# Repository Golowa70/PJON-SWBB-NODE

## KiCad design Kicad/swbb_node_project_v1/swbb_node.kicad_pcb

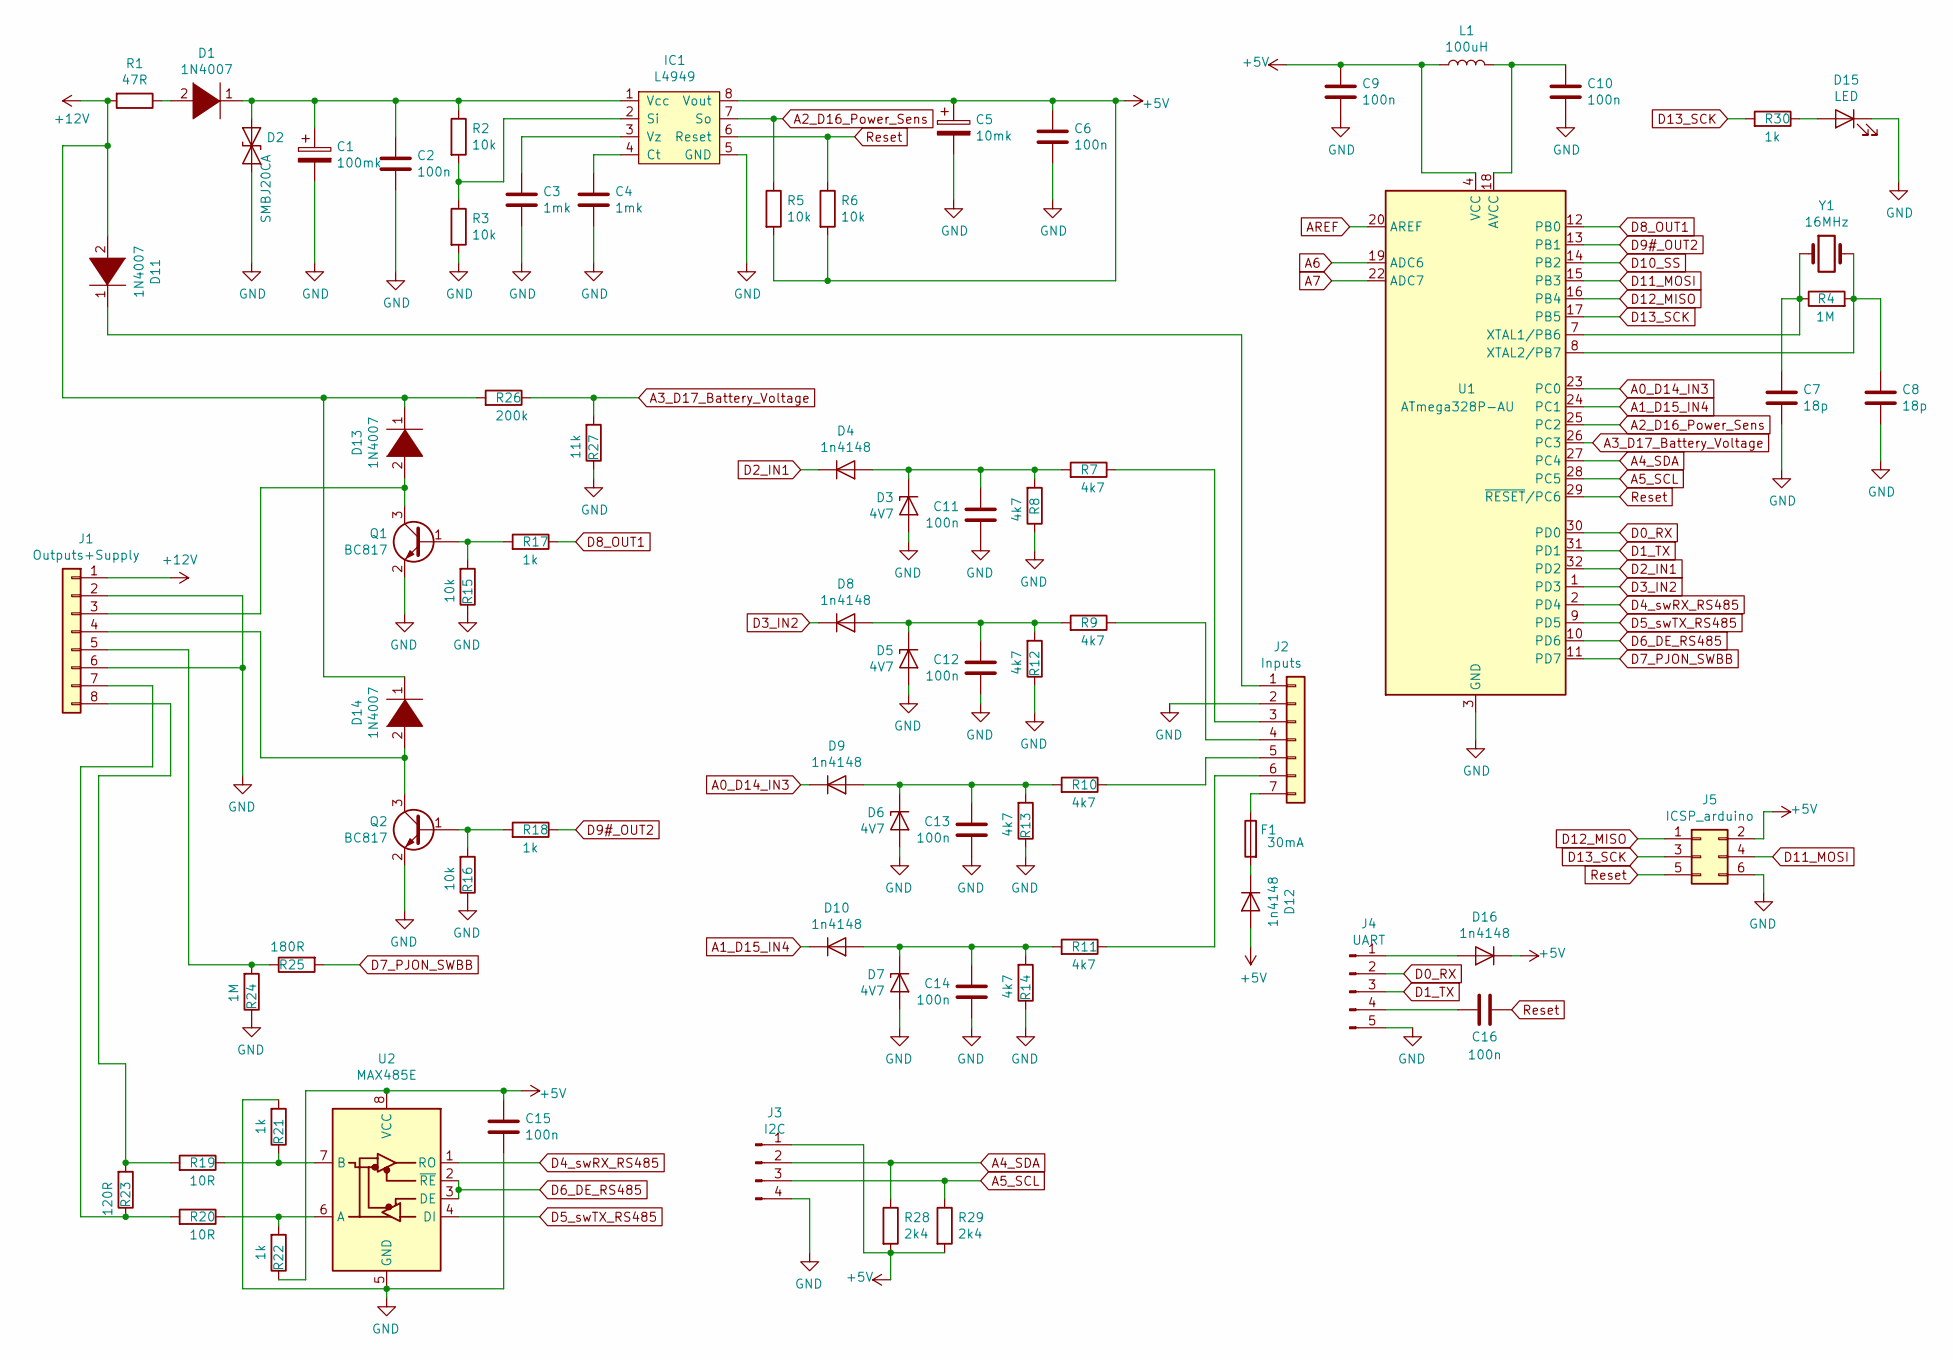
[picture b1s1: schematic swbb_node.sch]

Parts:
C1: 100mk; C_Elec_6.3x7.7
C2, C6, C9, C10, C11, C12, C13, C14, C15: 100n; C_0805_2012Metric
C3, C4: 1mk; C_1206_3216Metric
C5: 10mk; CP_EIA-7343-31_Kemet-D
C7, C8: 18p; C_1206_3216Metric
C16: 100n; C_0805_2012Metric_Pad1.15x1.40mm_HandSolder
D1, D11, D13, D14: 1N4007; D_SOD-123
D2: SMBJ20CA; D_SMB_Handsoldering
D3, D5, D6, D7: 4V7; D_1206_3216Metric_Pad1.42x1.75mm_HandSolder
D4, D8, D9, D10, D12, D16: 1n4148; D_1206_3216Metric_Pad1.42x1.75mm_HandSolder
D15: LED; LED_D3.0mm
F1: 30mA; Fuse_2010_5025Metric
IC1: L4949; SOIC-8_3.9x4.9mm_P1.27mm
J1: Outputs+Supply; JST_EH_S8B-EH_1x08_P2.50mm_Horizontal
J2: Inputs; JST_EH_S7B-EH_1x07_P2.50mm_Horizontal
J3: I2C; PinHeader_1x04_P2.54mm_Vertical
J4: UART; PinHeader_1x05_P2.54mm_Vertical
J5: ICSP_arduino; PinHeader_2x03_P2.54mm_Vertical
L1: 100uH; L_1210_3225Metric_Pad1.42x2.65mm_HandSolder
Q1, Q2: BC817; SOT-23
R1: 47R; R_2512_6332Metric
R2, R5, R6, R15, R16: 10k; R_0805_2012Metric_Pad1.15x1.40mm_HandSolder
R3: 10k; R_0805_2012Metric
R4, R24: 1M; R_0805_2012Metric_Pad1.15x1.40mm_HandSolder
R7, R8, R9, R10, R11, R12, R13, R14: 4k7; R_0805_2012Metric_Pad1.15x1.40mm_HandSolder
R17, R18, R21, R22: 1k; R_0805_2012Metric_Pad1.15x1.40mm_HandSolder
R19, R20: 10R; R_1206_3216Metric_Pad1.42x1.75mm_HandSolder
R23: 120R; R_1206_3216Metric_Pad1.42x1.75mm_HandSolder
R25: 180R; R_0805_2012Metric_Pad1.15x1.40mm_HandSolder
R26: 200k; R_0805_2012Metric_Pad1.15x1.40mm_HandSolder
R27: 11k; R_0805_2012Metric_Pad1.15x1.40mm_HandSolder
R28, R29: 2k4; R_0603_1608Metric_Pad1.05x0.95mm_HandSolder
R30: 1k; R_0603_1608Metric_Pad1.05x0.95mm_HandSolder
U1: ATmega328P-AU; TQFP-32_7x7mm_P0.8mm
U2: MAX485E; SO-8_3.9x4.9mm_P1.27mm
Y1: 16MHz; Crystal_HC49-U_Vertical

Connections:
+5V: C5.1, C6.1, C9.1, C15.1, D12.2 (A), D16.1 (K), IC1.8 (Vout), J3.1, J5.2 (+5V), L1.1, R5.2, R6.2, R22.1, R28.2, R29.2, U1.4 (VCC), U1.6 (VCC), U2.8 (VCC)
+12V: D11.2 (K), D13.1 (A), D14.1 (A), J1.1, R1.2, R26.2
A0_D14_IN3: D9.1 (K), U1.23 (PC0)
A1_D15_IN4: D10.1 (K), U1.24 (PC1)
A2_D16_Power_Sens: IC1.7 (So), R5.1, U1.25 (PC2)
A3_D17_Battery_Voltage: R26.1, R27.2, U1.26 (PC3)
A4_SDA: J3.2, R28.1, U1.27 (PC4)
A5_SCL: J3.3, R29.1, U1.28 (PC5)
A6: U1.19 (ADC6)
A7: U1.22 (ADC7)
AREF: U1.20 (AREF)
D0_RX: J4.2, U1.30 (PD0)
D1_TX: J4.3, U1.31 (PD1)
D2_IN1: D4.1 (K), U1.32 (PD2)
D3_IN2: D8.1 (K), U1.1 (PD3)
D4_swRX_RS485: U1.2 (PD4), U2.1 (RO)
D5_swTX_RS485: U1.9 (PD5), U2.4 (DI)
D6_DE_RS485: U1.10 (PD6), U2.2 (~RE), U2.3 (DE)
D7_PJON_SWBB: R25.2, U1.11 (PD7)
D8_OUT1: R17.1, U1.12 (PB0)
D9#_OUT2: R18.1, U1.13 (PB1)
D10_SS: U1.14 (PB2)
D11_MOSI: J5.4 (D11/MOSI), U1.15 (PB3)
D12_MISO: J5.1 (D12/MISO), U1.16 (PB4)
D13_SCK: J5.3 (D13/SCK), R30.2, U1.17 (PB5)
GND: C1.2, C2.2, C3.2, C4.2, C5.2, C6.2, C7.2, C8.1, C9.2, C10.2, C11.2, C12.2, C13.2, C14.2, C15.2, D2.2 (A2), D3.2 (A), D5.2 (A), D6.2 (A), D7.2 (A), D15.1 (K), IC1.5 (GND), J1.2, J1.6, J2.2, J3.4, J4.5, J5.6 (GND), Q1.2 (E), Q2.2 (E), R3.2, R8.1, R12.1, R13.1, R14.1, R15.1, R16.1, R21.2, R24.1, R27.1, U1.3 (GND), U1.5 (GND), U1.21 (GND), U2.5 (GND)
unnamed: C1.1, C2.1, D1.1 (A), D2.1 (A1), IC1.1 (Vcc), R2.1
unnamed: C3.1, IC1.3 (Vz)
unnamed: C4.1, IC1.4 (Ct)
unnamed: C7.1, R4.1, U1.7 (XTAL1/PB6), Y1.1
unnamed: C8.2, R4.2, U1.8 (XTAL2/PB7), Y1.2
unnamed: C10.1, L1.2, U1.18 (AVCC)
unnamed: C11.1, D3.1 (K), D4.2 (A), R7.2, R8.2
unnamed: C12.1, D5.1 (K), D8.2 (A), R9.2, R12.2
unnamed: C13.1, D6.1 (K), D9.2 (A), R10.2, R13.2
unnamed: C14.1, D7.1 (K), D10.2 (A), R11.2, R14.2
unnamed: C16.2, J4.4
unnamed: D1.2 (K), R1.1
unnamed: D11.1 (A), J2.1
unnamed: D12.1 (K), F1.2
unnamed: D13.2 (K), J1.3, Q1.3 (C)
unnamed: D14.2 (K), J1.4, Q2.3 (C)
unnamed: D15.2 (A), R30.1
unnamed: D16.2 (A), J4.1
unnamed: F1.1, J2.7
unnamed: IC1.2 (Si), R2.2, R3.1
unnamed: J1.5, R24.2, R25.1
unnamed: J1.7, R20.2, R23.1
unnamed: J1.8, R19.2, R23.2
unnamed: J2.3, R7.1
unnamed: J2.4, R9.1
unnamed: J2.5, R10.1
unnamed: J2.6, R11.1
unnamed: Q1.1 (B), R15.2, R17.2
unnamed: Q2.1 (B), R16.2, R18.2
unnamed: R19.1, R21.1, U2.7 (B)
unnamed: R20.1, R22.2, U2.6 (A)
Reset: C16.1, IC1.6 (Reset), J5.5 (RESET), R6.1, U1.29 (~RESET~/PC6)

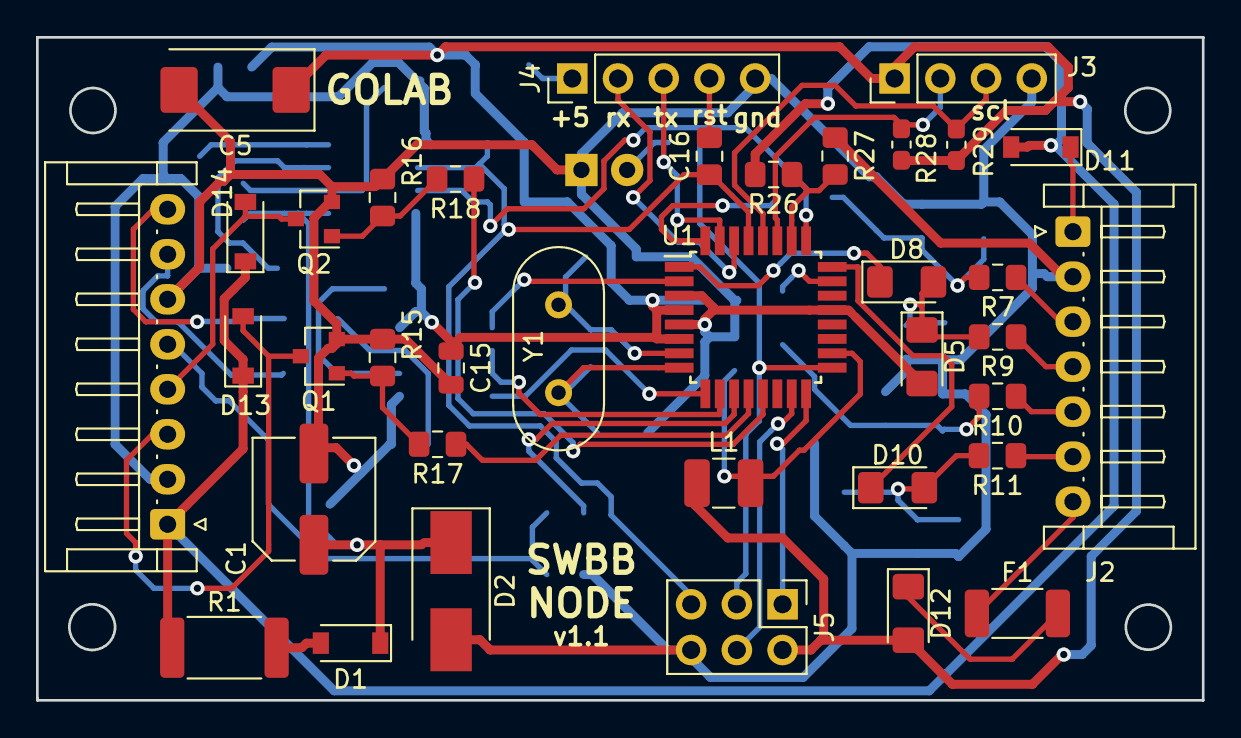
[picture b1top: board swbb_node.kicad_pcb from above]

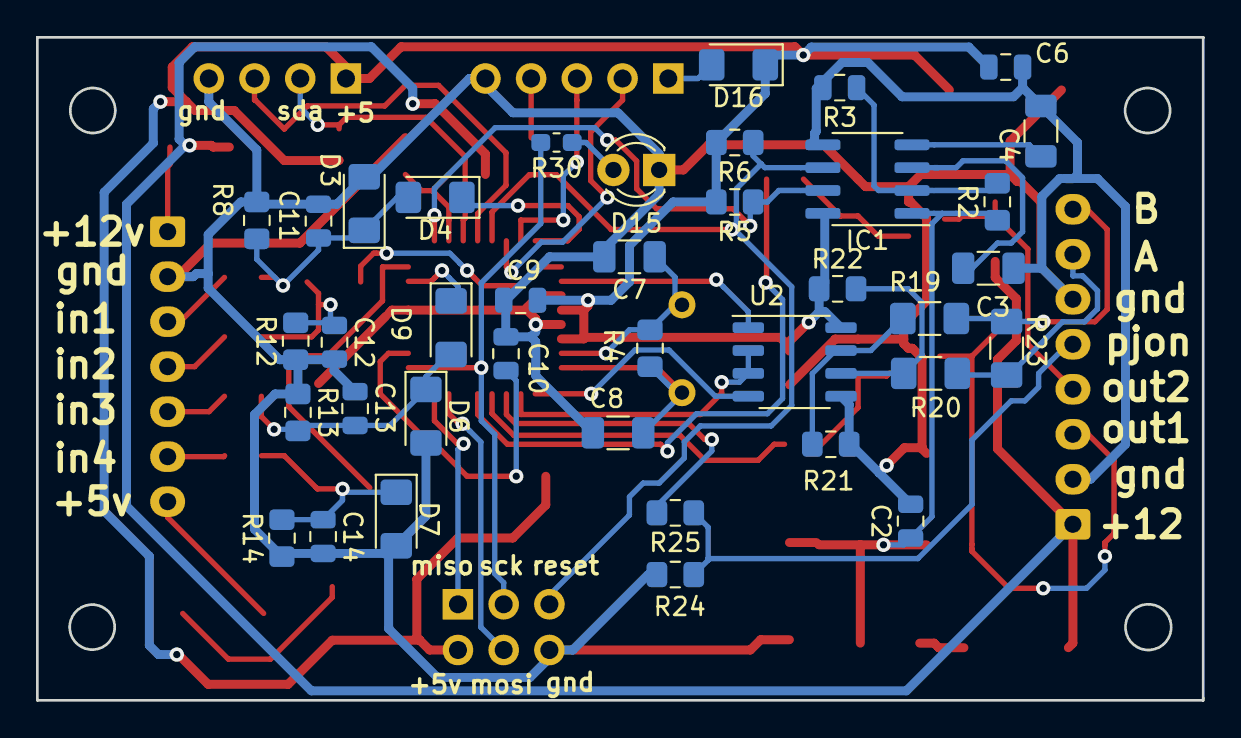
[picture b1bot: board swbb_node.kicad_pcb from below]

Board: 2 copper layers, 64.8 x 36.8 mm, 75 parts (38 on the bottom side), 54 nets.

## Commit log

2021-11-08 Added photo
